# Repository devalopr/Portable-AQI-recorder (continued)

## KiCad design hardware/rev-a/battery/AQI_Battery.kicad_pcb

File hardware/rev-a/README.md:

# AQI recorder — Rev A engineering review

Implemented in KiCad 10. Main PCB: **44 × 80 mm**. Battery PCB: **44 × 90 mm**. Both use four copper layers, with In1.Cu reserved for ground. The checked KiCad files are the authoritative routed design.

| Project | Open in KiCad | Schematic PDF |
|---|---|---|
| Main board | [AQI_Main.kicad_pro](main/AQI_Main.kicad_pro) | [Main schematic](main/review/AQI_Main.pdf) |
| 18650 supply | [AQI_Battery.kicad_pro](battery/AQI_Battery.kicad_pro) | [Battery schematic](battery/review/AQI_Battery.pdf) |

For Fusion fit checks, import [AQI_Main-fit-check.step](main/review/AQI_Main-fit-check.step). This assembly includes the optional CO₂ and e-paper components. The external display, PM sensor body, cables and enclosure must be added separately. The switch model is a simplified envelope.

This is an engineering review version. Fabrication release still requires the electrical, assembly and enclosure items below. Gerbers and an assembly-order package are intentionally not included.

Main-board front/rear PNGs now show all optional components, including CO₂ and e-paper parts. DNP flags remain intact in the BOM. Enable “Models marked DNP” in KiCad’s 3D viewer Appearance panel (shortcut D); this is a live viewer setting, independent of the saved PCB. Sensirion’s official SCD4x model and a simplified, dimensioned C&K switch model are included locally. Board previews do not include the external display, PM module, enclosure or battery holder; the complete enclosure assembly still needs checking. Right/left placement is specified from the front/display view, so the rear image is mirrored.

## Main board

- ESP32-C3-MINI-1-H4, at the lower left, with its integrated antenna facing the bottom edge and copper keepout on every layer (x = 0–15.7 mm, y = 73.8–80 mm).
- TFT flex wraps around the top edge to the rear **TE 1-84953-0, 10-way, 1 mm, top-contact** connector. Contacts face away from the PCB, as verified by the user. J5 is 9 mm lower than the earlier placement (origin y = 16.85 mm). The approach from the top edge is clear of components; verify the actual flex bend radius and connector engagement in the enclosure. The display body envelope is on Dwgs.User.
- Three front switches at x = 8, 22 and 36 mm, y = 66.25 mm. The power switch is on the right edge below the CO₂ island (origin x = 41.7 mm, y = 65.2 mm), with its actuator projecting outward. It disables the switched 5 V rail and downstream regulators.
- Bottom-right USB-C and adjacent front-mounted battery GH connector (origins x = 38.3 mm and 24.3 mm respectively). USB-C provides standalone power and ESP32 native USB. A TS3USB30E data switch selects the local port when local VBUS is present; otherwise it selects the internal link. TPS2116 isolates the two power sources. The data paths disconnect when neither host is present.
- TPS62160 regulators provide nominal 3.2 V for the MCU/TFT and about 3.33 V for SEN6x. The reduced core voltage gives the TFT supply margin below its 3.3 V upper limit.
- STCS05A current sink provides PWM backlight dimming; 1.5 Ω sets about 67 mA nominal. Validate brightness, current and backlight compliance against the actual display.
- Separate SEN5x and SEN6x connectors on the right edge, both rotated to put their actual mating openings outward to the right, prevent interchange of their 5 V and 3.3 V cables. Attach **one PM module**; the shared sensor address is 0x69.
- Optional SCD41 sits on a rear-right island (sensor origin y = 53 mm; island and both SEN connectors moved upward 4 mm), with two enclosed isolation slots, a 3 × 2 mm electrical bridge and two permanent 1.5 mm-wide outer-edge support tabs. Ground/power pours stop at the bridge; only four 0.15 mm traces cross it (power, ground, SDA and SCL). The outer tabs contain no copper on any layer; they add mechanical support but increase heat conduction through the laminate. Its TPS7A20 regulator stays on the main PCB; C16 decouples the sensor locally and C42 bypasses the regulator output. This reduces heat conduction; it does not eliminate self-heating or enclosure airflow effects. The CO₂ circuit remains DNP in the default assembly.
- GDEY037T03 e-paper connector J6 is at the opposite (left) upper edge, with its flex entry facing outward; its external boost circuit is provided as an alternate population. The TFT and e-paper share SPI, CS, DC and RESET: fit one display.

## Battery board

- MPD BH-18650-PC holder for a standard 65 mm unprotected cell.
- DW01A plus Fortune FS8205A implement cell overcharge, overdischarge and overcurrent protection. The selected FS8205A uses the **4.4 × 3 mm TSSOP-8** footprint.
- BQ24074 charger with power path. Attach a **10 kΩ cell-contact NTC** at J4; do not substitute a fixed resistor for the required temperature monitoring in an enclosed battery product.
- Charger defaults to USB100. MCP23008 at 0x21 controls EN1/EN2 and reads charge/input-present status. Configured charge-current ceiling is approximately 0.8 A; actual charging is bounded by input limit, load and thermal regulation.
- TPS61023 produces nominal 5.045 V and has a physical output-enable switch. TPS63031 provides the auxiliary 3.3 V output. Generic header design targets are 5 V / 0.5 A and 3.3 V / 0.3 A; these and the main board share the input/cell power budget and require load/thermal qualification.
- MAX17048 at 0x36 reports cell voltage and estimated state of charge through the shared I2C bus. Firmware reads SOC register 0x04 as an unsigned 8.8 percentage value; clamp the displayed value to 0–100%. Validate the gauge model and temperature compensation with the chosen cell.
- Battery-side I2C pullups R18/R19 are DNP when connected to the main board. The main board supplies 3.2 V pullups.
- Cell-negative is isolated from system GND by the protection FETs. Do not bypass this separation with a cable, mounting hardware or an external ground connection.
- The holder requires correct polarity. Reverse-cell insertion protection is not implemented. The 3.3 V control supply remains active when the 5 V output switch is off; remove the cell for long-term storage.

## Internal cable

Use **JST GH 10-way**, side-entry SM10B-GHS-TB headers and matching GHR-10V-S housings/appropriate GH crimp contacts. Wire pin 1 to pin 1; verify continuity rather than relying on an off-the-shelf cable's apparent orientation. Start with a harness no longer than 50 mm, using suitable 26–28 AWG contacts/wire and a twisted D+/D− pair where practical. Check USB operation with the final harness.

| Pin | Signal | Direction |
|---|---|---|
| 1, 2 | Regulated 5 V | Battery → main |
| 3 | GND | Common |
| 4 | USB D− | Bidirectional |
| 5 | USB D+ | Bidirectional |
| 6 | GND | Common |
| 7 | I2C SDA | Bidirectional |
| 8 | I2C SCL | Main → battery |
| 9 | GND | Common |
| 10 | External USB host present | Battery → main |

The battery USB-C is a sink/data port. USB CC termination stays at each external receptacle; CC is not carried through GH. The main board's internal GH input is not another USB-C receptacle and needs no additional CC termination. Both external ports are isolated by the main-board switching circuits.

SEN5x J3: 1 = 5 V, 2 = GND, 3 = SDA, 4 = SCL, 5 = GND, 6 = NC. SEN6x J4 uses a **custom 4-to-6 cable**: 1 = 3.3 V, 2 = GND, 3 = SDA, 4 = SCL; sensor pins 5/6 remain open. Do not use the battery GH cable for a sensor.

## Display population

Default handheld assembly: populate J5 and the backlight circuit; leave e-paper parts DNP. The optional SCD41 circuit is separately selectable.

E-paper assembly: populate J6, L3, Q3, D10–D12, R30/R31 and C30–C36/C38–C41. Keep R32 fitted for the reference circuit's BS-low setting. J7 is a high-level override: remove R32 before bridging J7. Leave J5 and the backlight circuit unpopulated. Confirm the exact panel revision, flex thickness/contact orientation and BS setting against the purchased panel before assembly. The vendor pin table and reference drawing disagree about BS; this is a release item, not a resolved assumption.

The ESP32 pin allocation supports ESPHome. The exact GDEY037T03/UC8253 driver has not been validated in ESPHome; GxEPD2 has a panel driver, but using that Arduino driver does not by itself provide an ESPHome component. The repository's current prototype firmware also needs the Rev A GPIO map, MCP23008 buttons and fuel-gauge integration. See [firmware integration](firmware/README.md).

## Checks and release items

The final review includes KiCad ERC, DRC with schematic parity, an independent comparison of every connected pin against design.json, schematic PDFs, board renders and engineering BOMs. See [validation.json](validation.json) for actual results and checked file hashes. A clean DRC confirms geometry/connectivity rules; it does not validate a circuit's analogue performance or the enclosure.

Before fabrication release:

1. Finish the enclosure CAD: TFT bend radius, connector latch access, button caps/travel, PCB retention, sensor airflow and battery-holder clearance. No PCB mounting holes are included; the current outline assumes enclosure rails/retainers. Support the CO₂ island without a conductive metal bridge or force on the sensor. Check the isolation-slot tool radius and island strength with the fabricator; provide local enclosure support clear of the sensor opening.
2. Qualify the integrated antenna in the final enclosure. The TFT body spans x = 0.64–43.36 mm, y = 1.5–62.46 mm. The revised antenna spans approximately x = 2.4–15.6 mm, y = 74.1–79.5 mm, so it no longer lies behind the display. The nominal display-to-antenna gap is about 11.6 mm; the button and adjacent GH connector metal are closer. This 44 × 80 mm layout does **not** provide [Espressif's recommended 15 mm clearance in all directions](https://docs.espressif.com/projects/esp-hardware-design-guidelines/en/latest/esp32c3/pcb-layout-design.html#general-principles-of-pcb-layout-for-modules-positioning-a-module-on-a-base-board). Keep the cell, sensor bodies, cables, fasteners and enclosure metal away from the antenna. Measure Wi-Fi/BLE performance with the final LCD or e-paper assembly; copper keepouts alone do not establish RF performance. The integrated-antenna module is retained as requested; no external antenna substitution is made.
3. Qualify USB current and inrush. Standalone sensing requires a suitable 5 V supply (start with a rated 1 A or higher adapter). The main board does not detect Type-C advertised current. The battery board starts at 100 mA; firmware must establish the allowed source current before selecting 500 mA or resistor-programmed mode. Do not assume every host port permits 1 A. Verify boot/measurement with the battery absent and depleted, plus both-port plug/unplug transitions.
4. Review exact MLCC/inductor ordering codes, effective capacitance under DC bias, component substitutions and assembly availability. The CSVs are engineering BOMs, not approved JLCPCB assembly BOMs. In particular, verify the e-paper flying capacitor at its operating voltage.
5. Check battery protection thresholds against the selected cell, charge/discharge operation, cell NTC limits, output overload behaviour and temperatures in the enclosure. Review exposed-pad thermal vias and stencil/tenting with the assembler.
6. Validate CO₂ temperature offset with Wi-Fi, the display and PM sensor operating. Couple the CO₂ opening to ambient air and shield it from PM fan turbulence. Validate USB signal quality, regulator transients, backlight PWM, e-paper power sequencing/BS setting and the exact ESPHome display driver on hardware.

## Sources and reproducibility

The selected circuits were checked against manufacturer datasheets retained under references/datasheets. Main sources include [Espressif module documentation](https://documentation.espressif.com/esp32-c3-mini-1_datasheet_en.html), [TI BQ24074](https://www.ti.com/lit/ds/symlink/bq24074.pdf), [TI TPS61023](https://www.ti.com/lit/ds/symlink/tps61023.pdf), [ADI MAX17048](https://www.analog.com/media/en/technical-documentation/data-sheets/max17048-max17049.pdf), and the [Good Display reference document](https://ecksteinimg.de/Photo/GD03042/GDEY037T03-T02.pdf?_t=1768267937). [GxEPD2](https://github.com/ZinggJM/GxEPD2) lists the exact panel; the [ESPHome UC8253 discussion](https://github.com/orgs/esphome/discussions/3504) documents the integration gap.

Run `python3 scripts/refresh_review.py --render` with KiCad 10 installed to refresh checks, PDF/SVG/BOM exports and native board PNGs from the current KiCad files. The script accepts `--cli` and `--pcb-python` overrides; the latter must provide KiCad's pcbnew module. It does not regenerate the boards. Early research and construction helpers are retained for traceability; rebuilding from their intermediate inputs can erase or replace the manually finished routing.

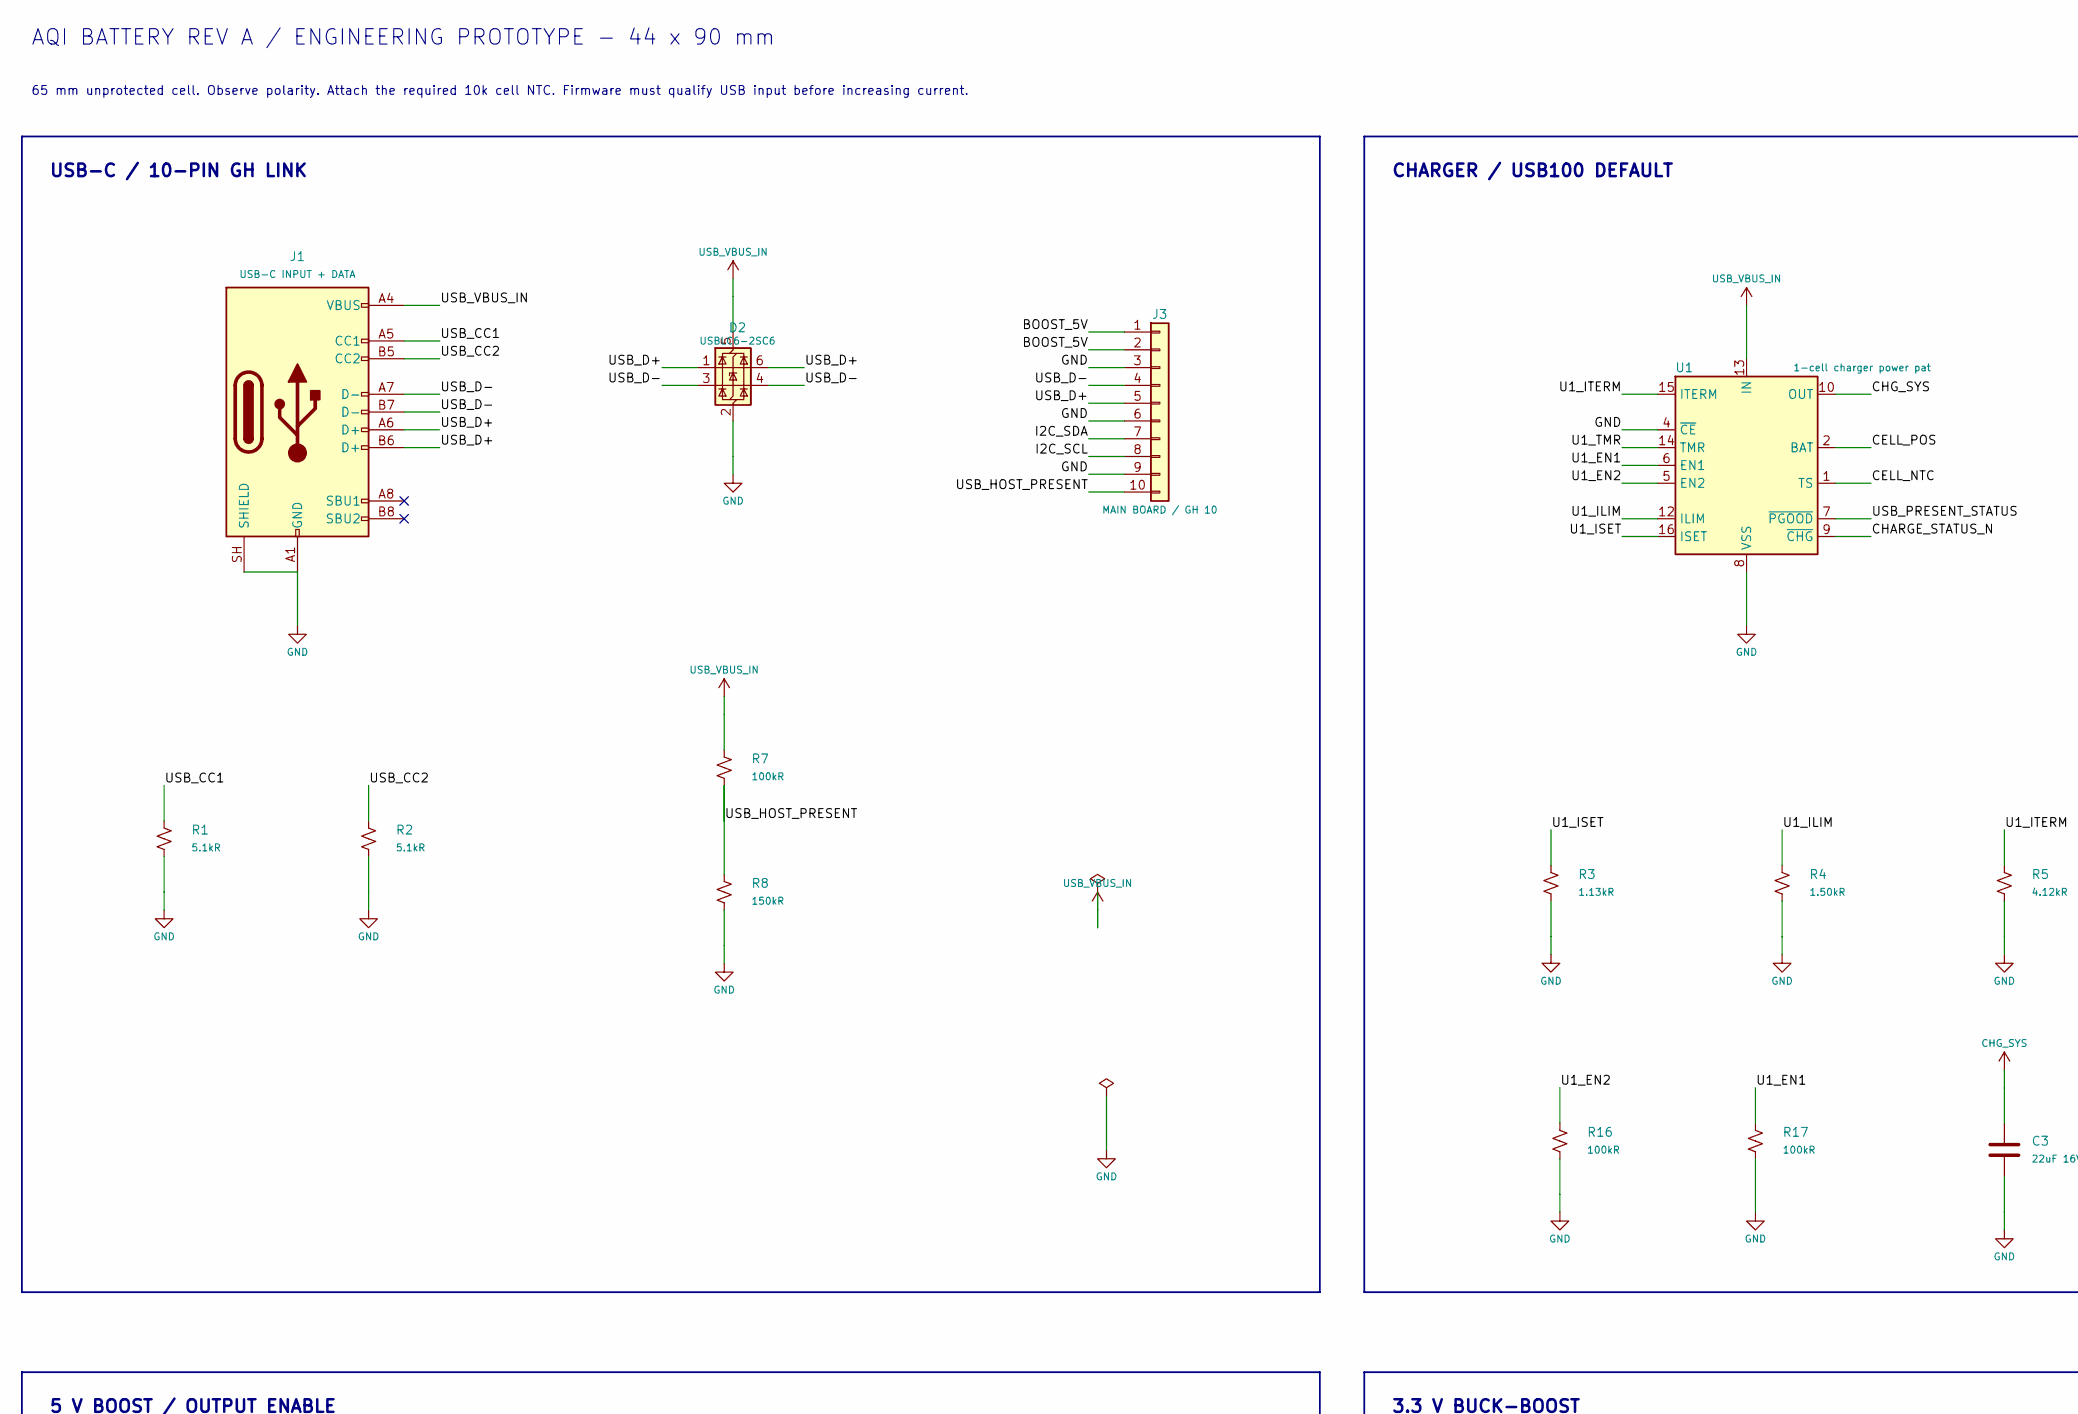
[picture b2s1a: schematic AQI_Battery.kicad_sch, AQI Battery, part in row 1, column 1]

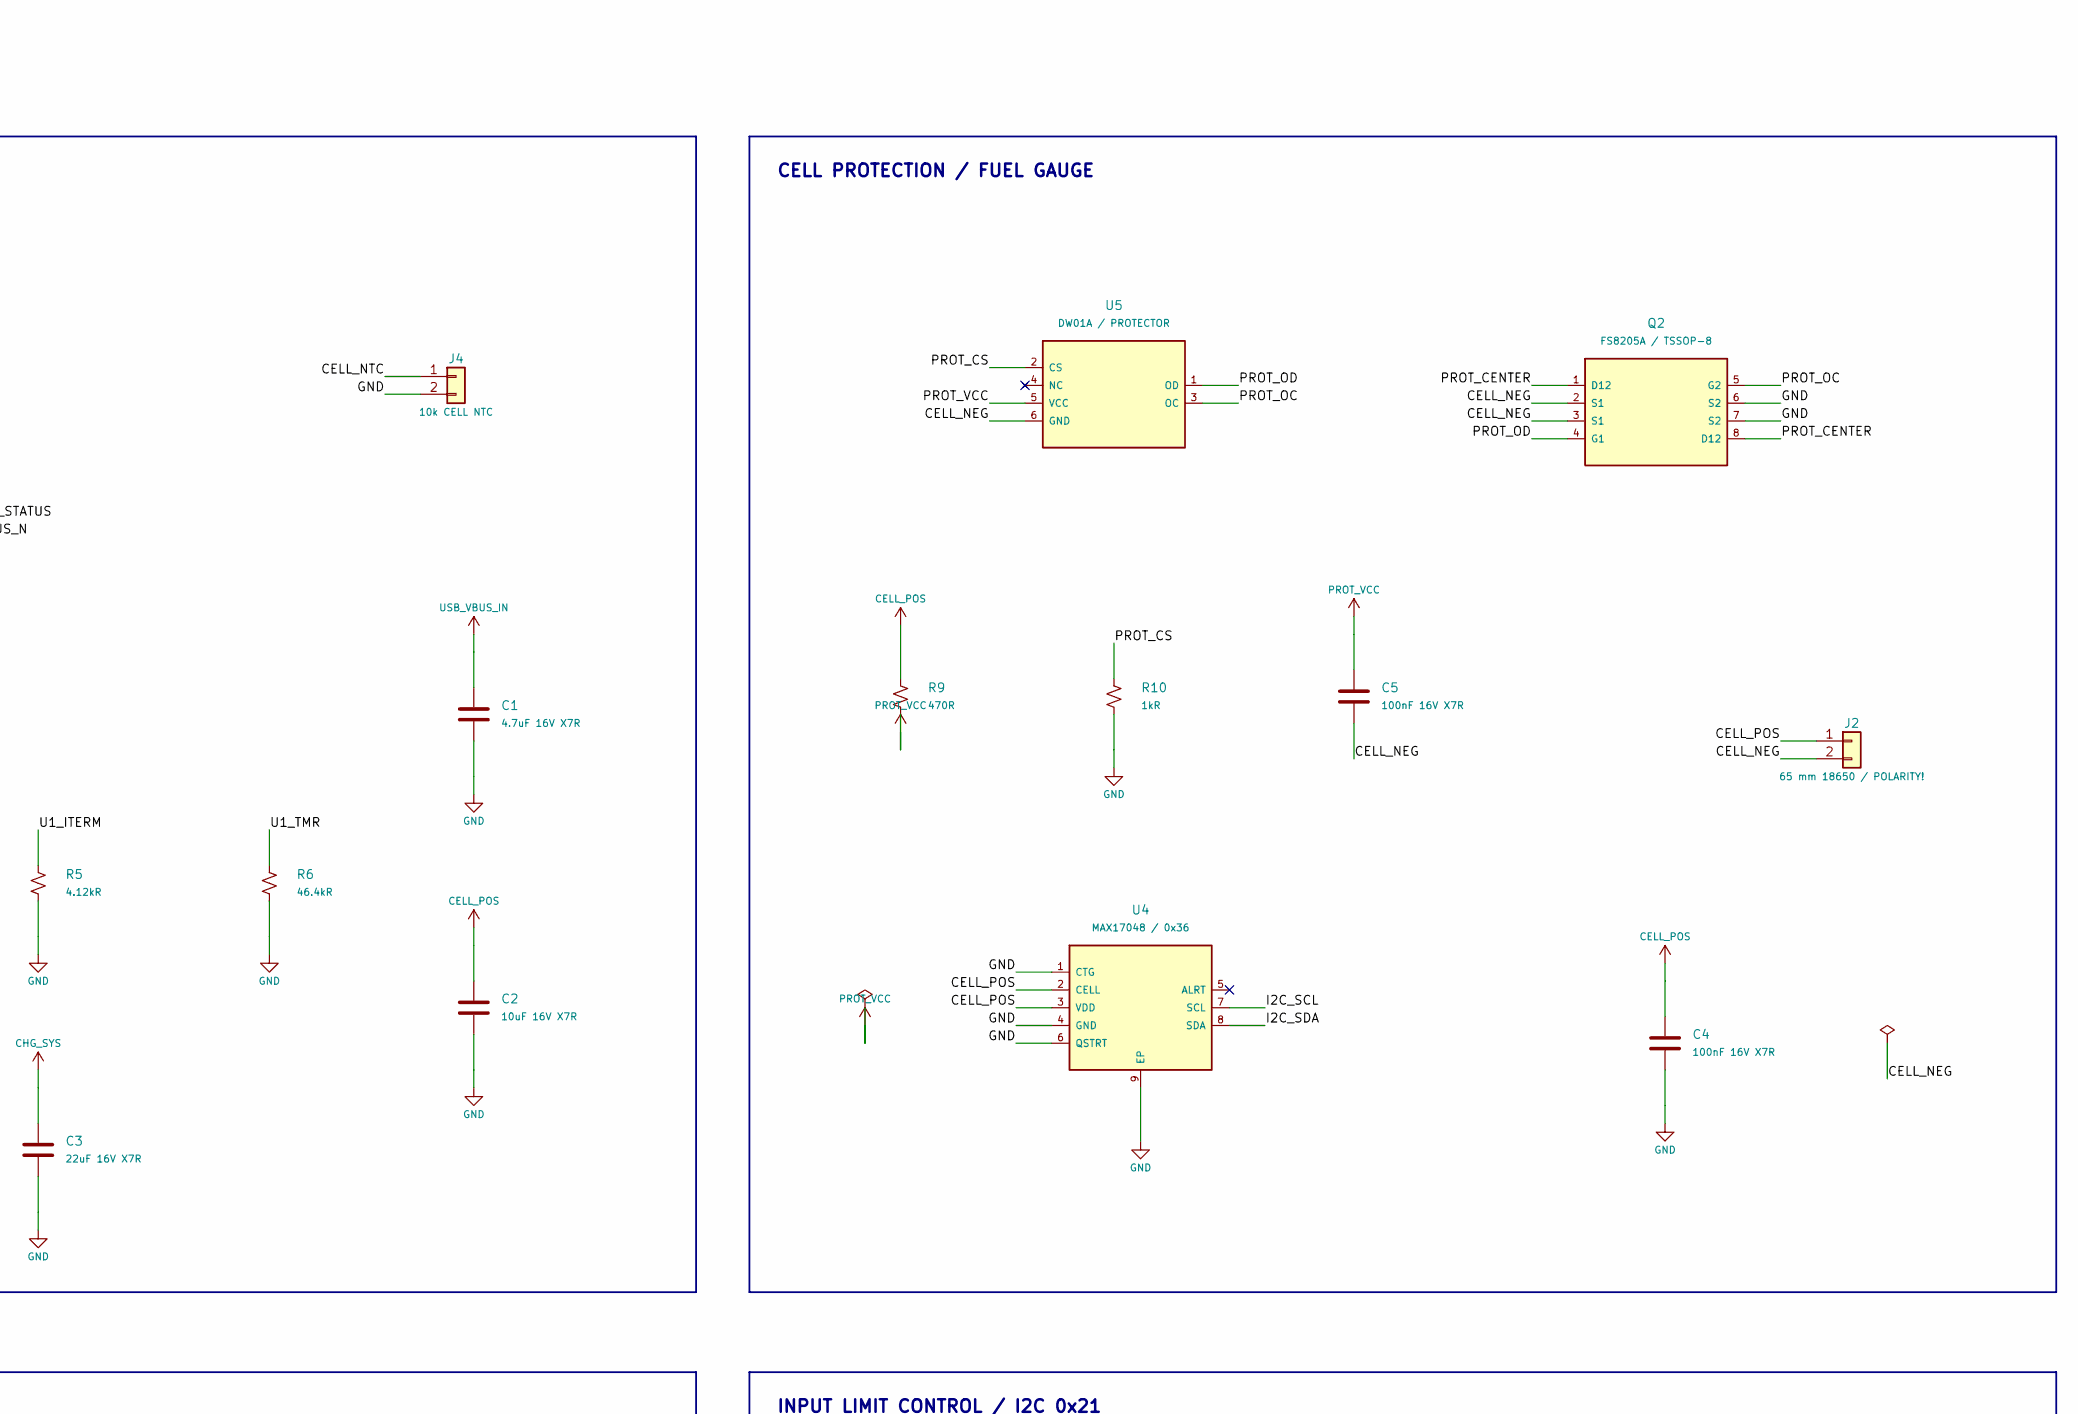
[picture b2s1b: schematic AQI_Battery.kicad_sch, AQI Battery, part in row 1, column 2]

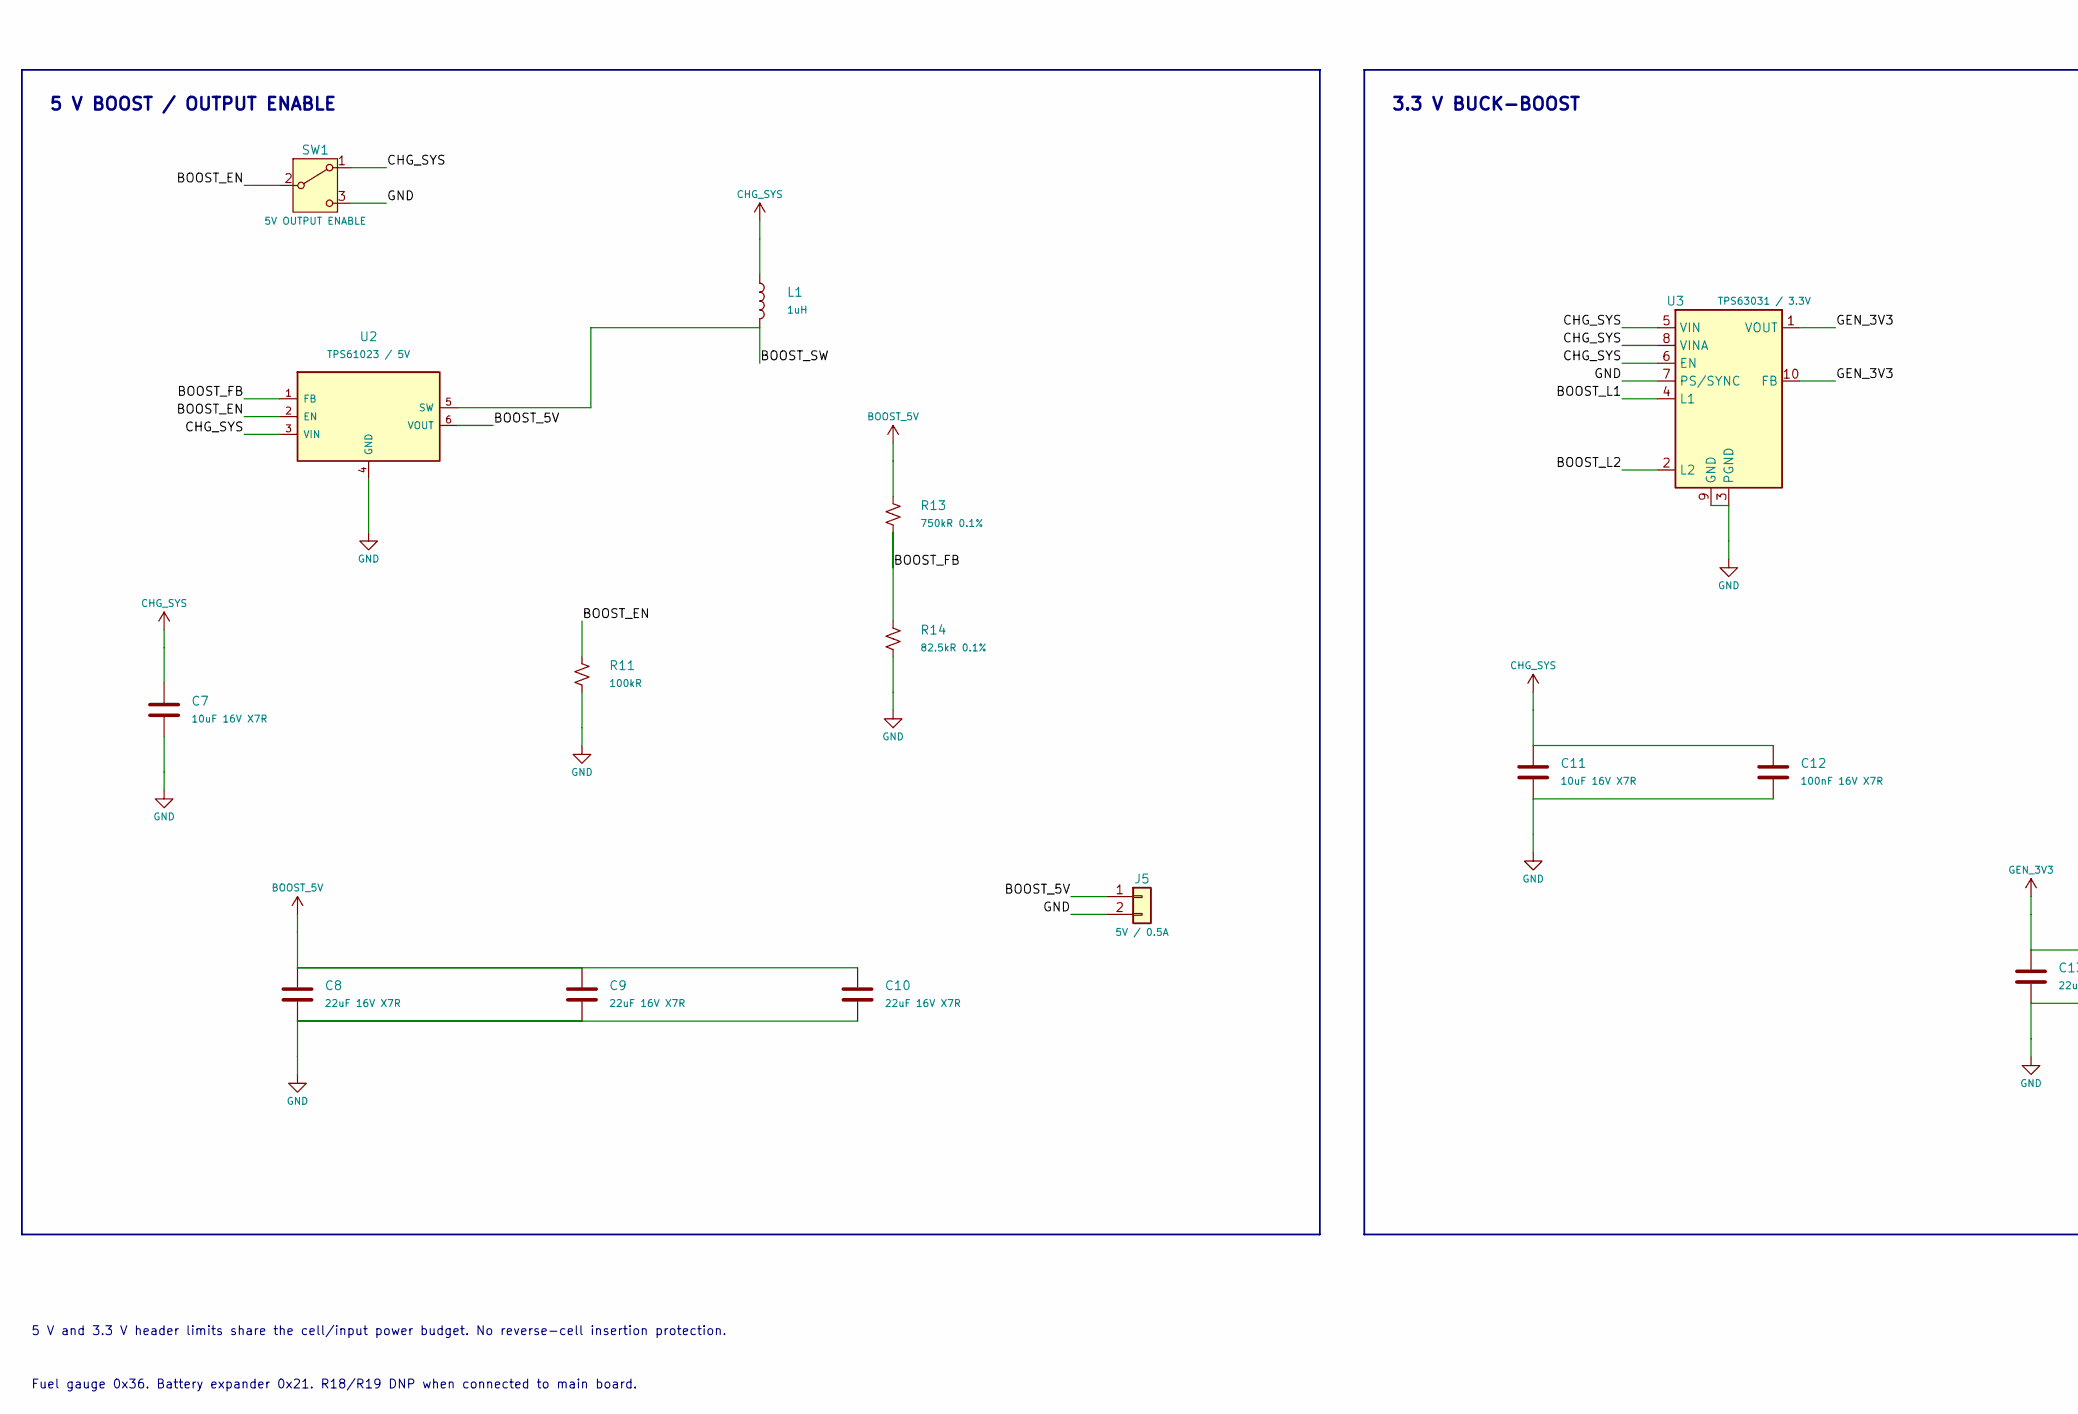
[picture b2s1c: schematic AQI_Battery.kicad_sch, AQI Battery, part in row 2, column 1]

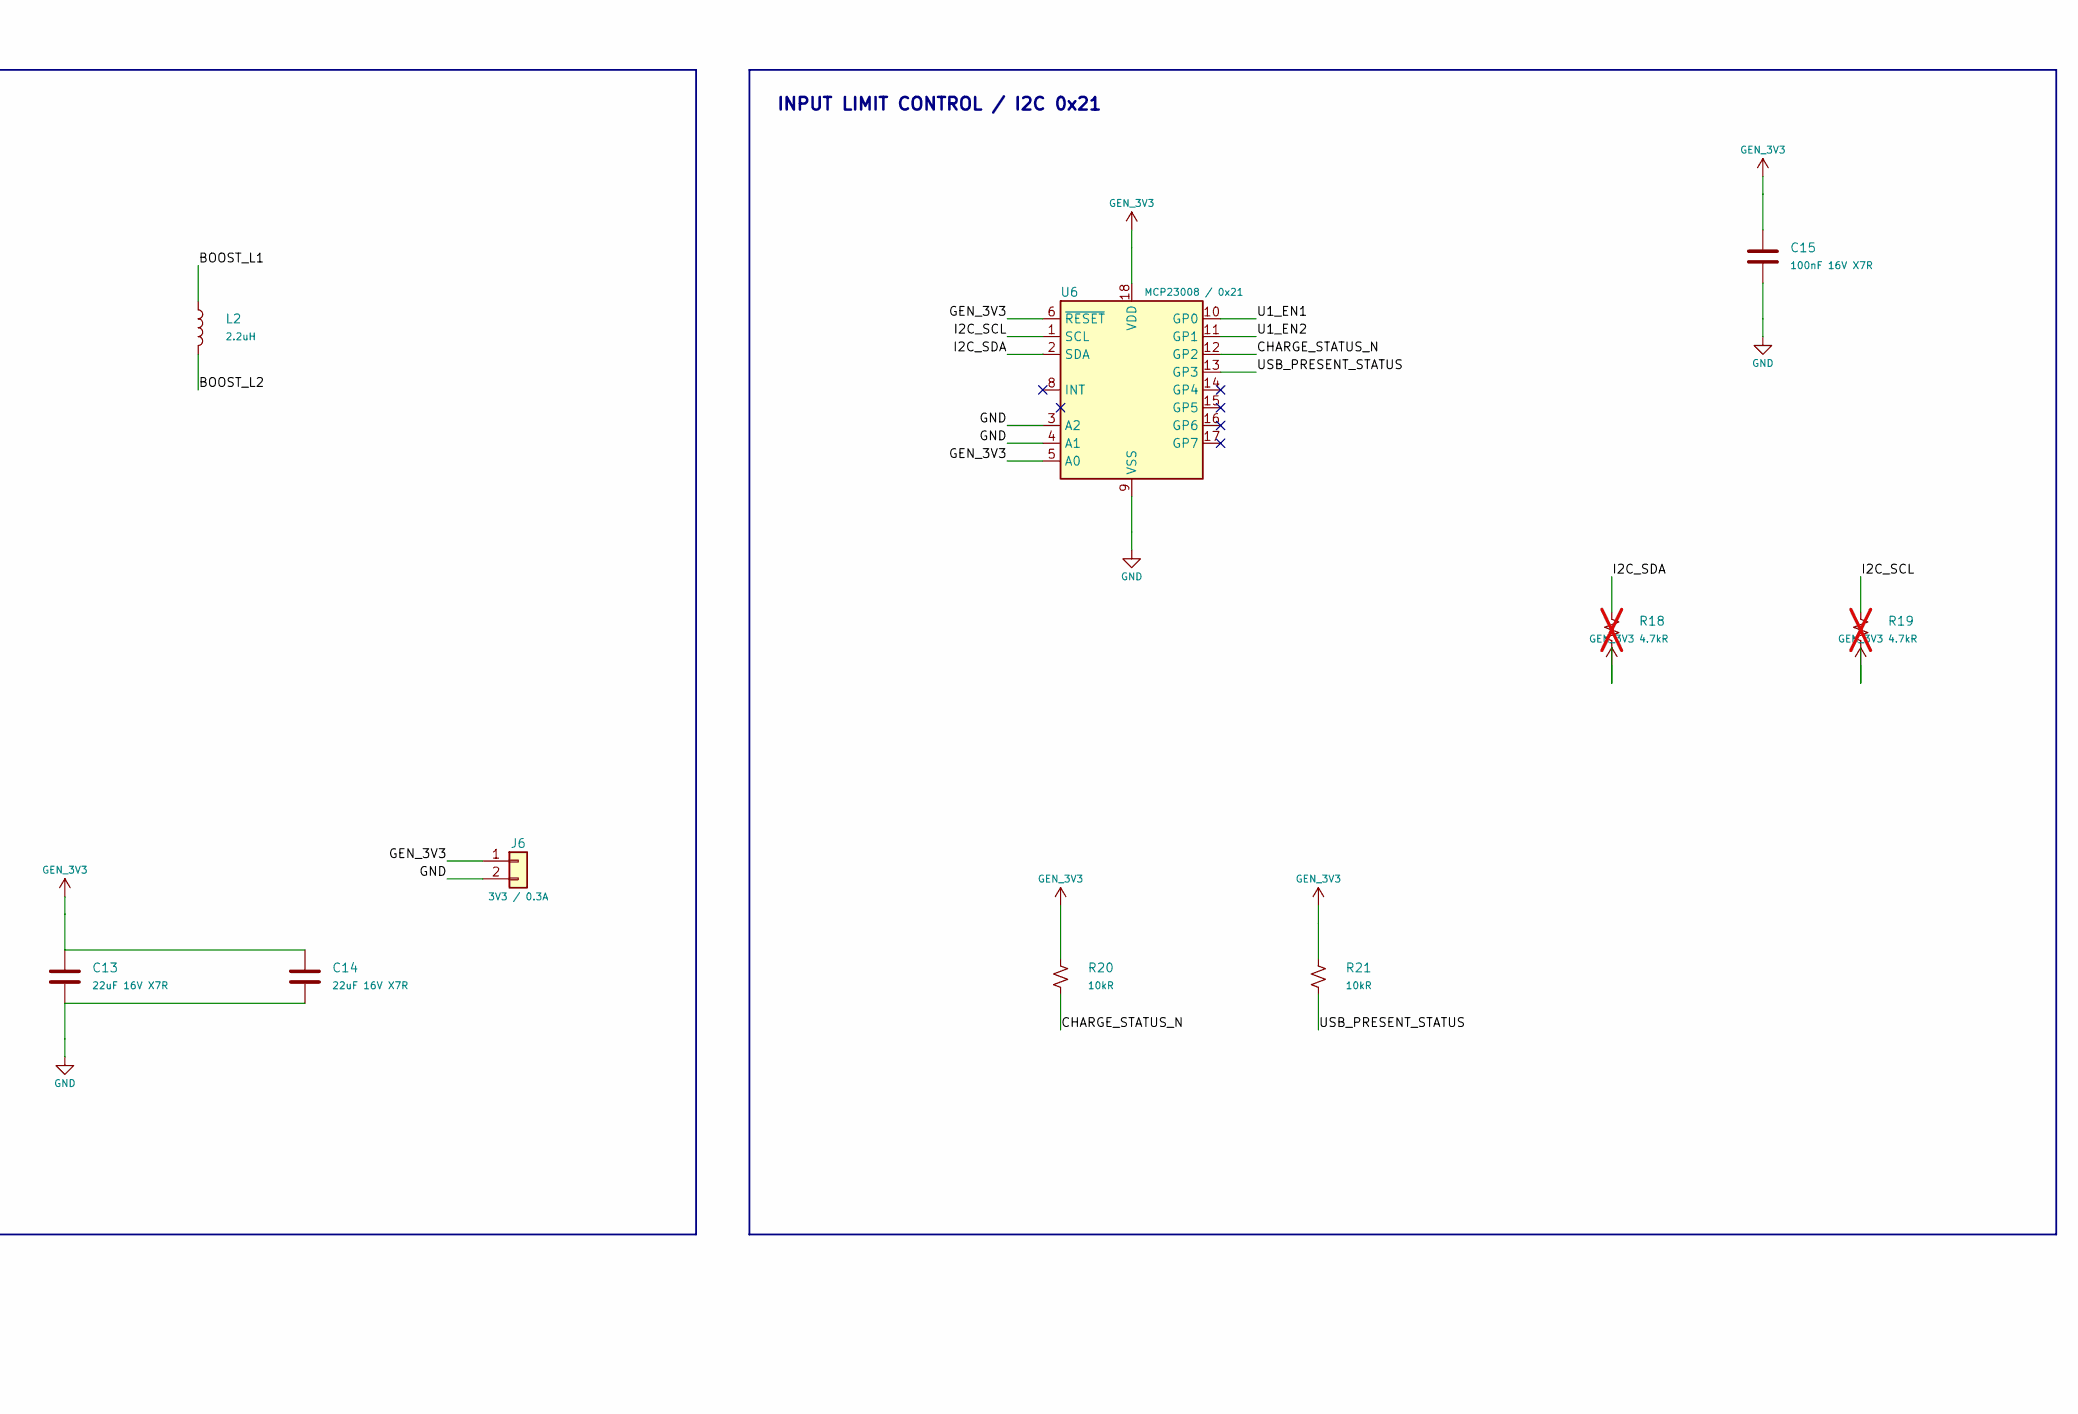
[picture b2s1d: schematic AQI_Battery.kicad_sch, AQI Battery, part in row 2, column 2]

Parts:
C1: 4.7uF 16V X7R; C_0805_2012Metric; MPN TBD
C2, C7, C11: 10uF 16V X7R; C_0805_2012Metric; MPN TBD
C3, C8, C9, C10, C13, C14: 22uF 16V X7R; C_0805_2012Metric; MPN TBD
C4, C5, C12: 100nF 16V X7R; C_0603_1608Metric; MPN TBD
C15: 100nF 16V X7R; C_0603_1608Metric
D2: USBLC6-2SC6; SOT-23-6; MPN USBLC6-2SC6
J1: USB-C INPUT + DATA; USB_C_Receptacle_GCT_USB4105-xx-A_16P_TopMnt_Horizontal; MPN USB4105-GF-A
J2: 65 mm 18650 / POLARITY!; BatteryHolder_MPD_BH-18650-PC; MPN BH-18650-PC
J3: MAIN BOARD / GH 10; JST_GH_SM10B-GHS-TB_1x10-1MP_P1.25mm_Horizontal; MPN SM10B-GHS-TB
J4: 10k CELL NTC; JST_GH_SM02B-GHS-TB_1x02-1MP_P1.25mm_Horizontal; MPN SM02B-GHS-TB(LF)(SN)
J5: 5V / 0.5A; PinHeader_1x02_P2.54mm_Vertical; MPN Pin header 1x2 P2.54
J6: 3V3 / 0.3A; PinHeader_1x02_P2.54mm_Vertical; MPN Pin header 1x2 P2.54
L1: 1uH; L_Coilcraft_XAL5030-XXX; MPN XAL5030-102MEC
L2: 2.2uH; L_Coilcraft_XAL4020-XXX; MPN XAL4020-222MEC
Q2: FS8205A / TSSOP-8; TSSOP-8_4.4x3mm_P0.65mm; MPN FS8205A
R1, R2: 5.1kR; R_0603_1608Metric; MPN TBD
R3: 1.13kR; R_0603_1608Metric; MPN TBD
R4: 1.50kR; R_0603_1608Metric; MPN TBD
R5: 4.12kR; R_0603_1608Metric; MPN TBD
R6: 46.4kR; R_0603_1608Metric; MPN TBD
R7, R11, R16, R17: 100kR; R_0603_1608Metric; MPN TBD
R8: 150kR; R_0603_1608Metric; MPN TBD
R9: 470R; R_0603_1608Metric; MPN TBD
R10: 1kR; R_0603_1608Metric; MPN TBD
R13: 750kR 0.1%; R_0603_1608Metric; MPN TBD
R14: 82.5kR 0.1%; R_0603_1608Metric; MPN TBD
R18, R19: 4.7kR; R_0603_1608Metric; MPN TBD; not fitted
R20, R21: 10kR; R_0603_1608Metric
SW1: 5V OUTPUT ENABLE; SW_SPDT_CK_JS102011SAQN; MPN JS102011SAQN
U1: 1-cell charger power pat; VQFN-16-1EP_3x3mm_P0.5mm_EP1.6x1.6mm; MPN BQ24074RGT
U2: TPS61023 / 5V; SOT-563; MPN TPS61023DRLR
U3: TPS63031 / 3.3V; WSON-10-1EP_2.5x2.5mm_P0.5mm_EP1.2x2mm; MPN TPS63031DSKR
U4: MAX17048 / 0x36; TDFN-8-1EP_2x2mm_P0.5mm_EP0.8x1.2mm; MPN MAX17048G+T10
U5: DW01A / PROTECTOR; SOT-23-6; MPN DW01A
U6: MCP23008 / 0x21; SOIC-18W_7.5x11.6mm_P1.27mm; MPN MCP23008T-E/SO

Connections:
/BOOST_EN: R11.1, SW1.2 (B), U2.2 (EN)
/BOOST_FB: R13.2, R14.1, U2.1 (FB)
/BOOST_L1: L2.1, U3.4 (L1)
/BOOST_L2: L2.2, U3.2 (L2)
/BOOST_SW: L1.2, U2.5 (SW)
/CELL_NEG: C5.2, J2.2, Q2.2 (S1), Q2.3 (S1), U5.6 (GND)
/CELL_NTC: J4.1, U1.1 (TS)
/CHARGE_STATUS_N: R20.2, U1.9 (~CHG), U6.12 (GP2)
/I2C_SCL: J3.8, R19.1, U4.7 (SCL), U6.1 (SCL)
/I2C_SDA: J3.7, R18.1, U4.8 (SDA), U6.2 (SDA)
/PROT_CENTER: Q2.1 (D12), Q2.8 (D12)
/PROT_CS: R10.1, U5.2 (CS)
/PROT_OC: Q2.5 (G2), U5.3 (OC)
/PROT_OD: Q2.4 (G1), U5.1 (OD)
/U1_EN1: R17.1, U1.6 (EN1), U6.10 (GP0)
/U1_EN2: R16.1, U1.5 (EN2), U6.11 (GP1)
/U1_ILIM: R4.1, U1.12 (ILIM)
/U1_ISET: R3.1, U1.16 (ISET)
/U1_ITERM: R5.1, U1.15 (ITERM)
/U1_TMR: R6.1, U1.14 (TMR)
/USB_CC1: J1.A5 (CC1), R1.1
/USB_CC2: J1.B5 (CC2), R2.1
/USB_D+: D2.1 (I/O1), D2.6 (I/O1), J1.A6 (D+), J1.B6 (D+), J3.5
/USB_D-: D2.3 (I/O2), D2.4 (I/O2), J1.A7 (D-), J1.B7 (D-), J3.4
/USB_HOST_PRESENT: J3.10, R7.2, R8.1
/USB_PRESENT_STATUS: R21.2, U1.7 (~PGOOD), U6.13 (GP3)
BOOST_5V: C8.1, C9.1, C10.1, J3.1, J3.2, J5.1, R13.1, U2.6 (VOUT)
CELL_POS: C2.1, C4.1, J2.1, R9.1, U1.2 (BAT), U1.3 (BAT), U4.2 (CELL), U4.3 (VDD)
CHG_SYS: C3.1, C7.1, C11.1, C12.1, L1.1, SW1.1 (A), U1.10 (OUT), U1.11 (OUT), U2.3 (VIN), U3.5 (VIN), U3.6 (EN), U3.8 (VINA)
GEN_3V3: C13.1, C14.1, C15.1, J6.1, R18.2, R19.2, R20.1, R21.1, U3.1 (VOUT), U3.10 (FB), U6.5 (A0), U6.6 (~RESET), U6.18 (VDD)
GND: C1.2, C2.2, C3.2, C4.2, C7.2, C8.2, C9.2, C10.2, C11.2, C12.2, C13.2, C14.2, C15.2, D2.2 (GND), J1.A1 (GND), J1.A12 (GND), J1.B1 (GND), J1.B12 (GND), J1.SH (SHIELD), J3.3, J3.6, J3.9, J4.2, J5.2, J6.2, Q2.6 (S2), Q2.7 (S2), R1.2, R2.2, R3.2, R4.2, R5.2, R6.2, R8.2, R10.2, R11.2, R14.2, R16.2, R17.2, SW1.3 (C), U1.4 (~CE), U1.8 (VSS), U1.17 (VSS), U2.4 (GND), U3.3 (PGND), U3.7 (PS/SYNC), U3.9 (GND), U3.11 (PGND), U4.1 (CTG), U4.4 (GND), U4.6 (QSTRT), U4.9 (EP), U6.3 (A2), U6.4 (A1), U6.9 (VSS)
PROT_VCC: C5.1, R9.2, U5.5 (VCC)
USB_VBUS_IN: C1.1, D2.5 (VBUS), J1.A4 (VBUS), J1.A9 (VBUS), J1.B4 (VBUS), J1.B9 (VBUS), R7.1, U1.13 (IN)

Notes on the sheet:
USB-C / 10-PIN GH LINK
CHARGER / USB100 DEFAULT
CELL PROTECTION / FUEL GAUGE
5 V BOOST / OUTPUT ENABLE
3.3 V BUCK-BOOST
INPUT LIMIT CONTROL / I2C 0x21
AQI BATTERY REV A / ENGINEERING PROTOTYPE - 44 x 90 mm
65 mm unprotected cell. Observe polarity. Attach the required 10k cell NTC. Firmware must qualify USB input before increasing current.
5 V and 3.3 V header limits share the cell/input power budget. No reverse-cell insertion protection.
Fuel gauge 0x36. Battery expander 0x21. R18/R19 DNP when connected to main board.

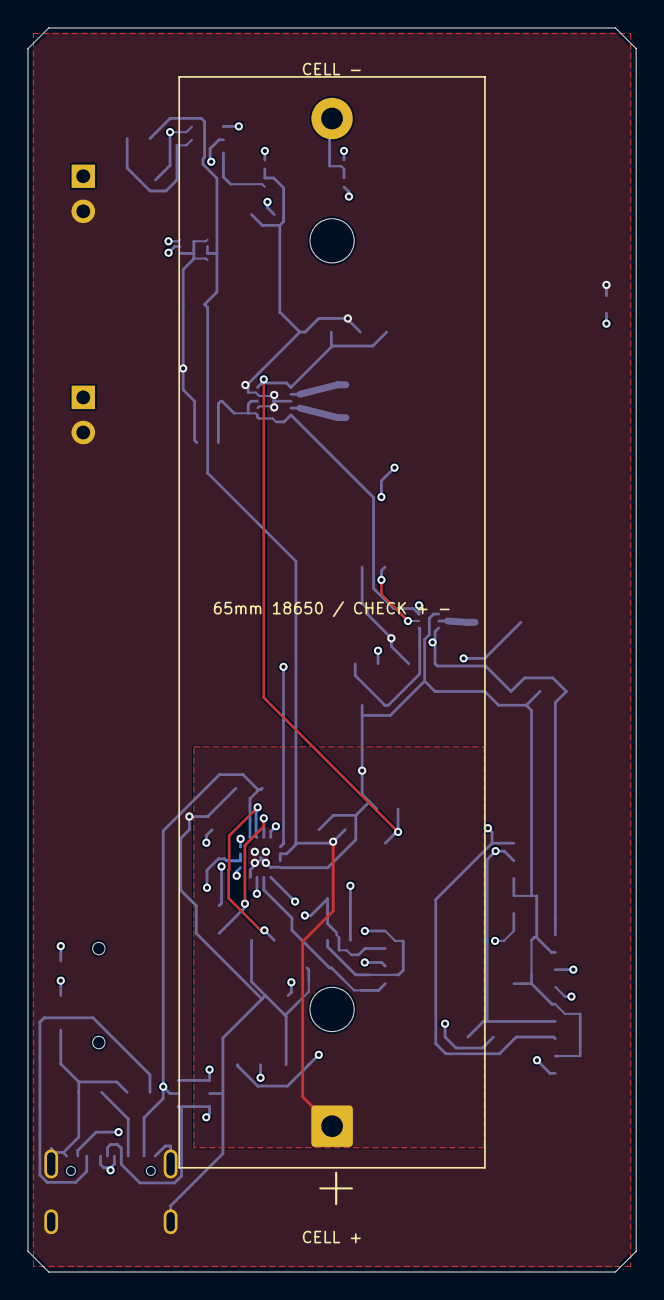
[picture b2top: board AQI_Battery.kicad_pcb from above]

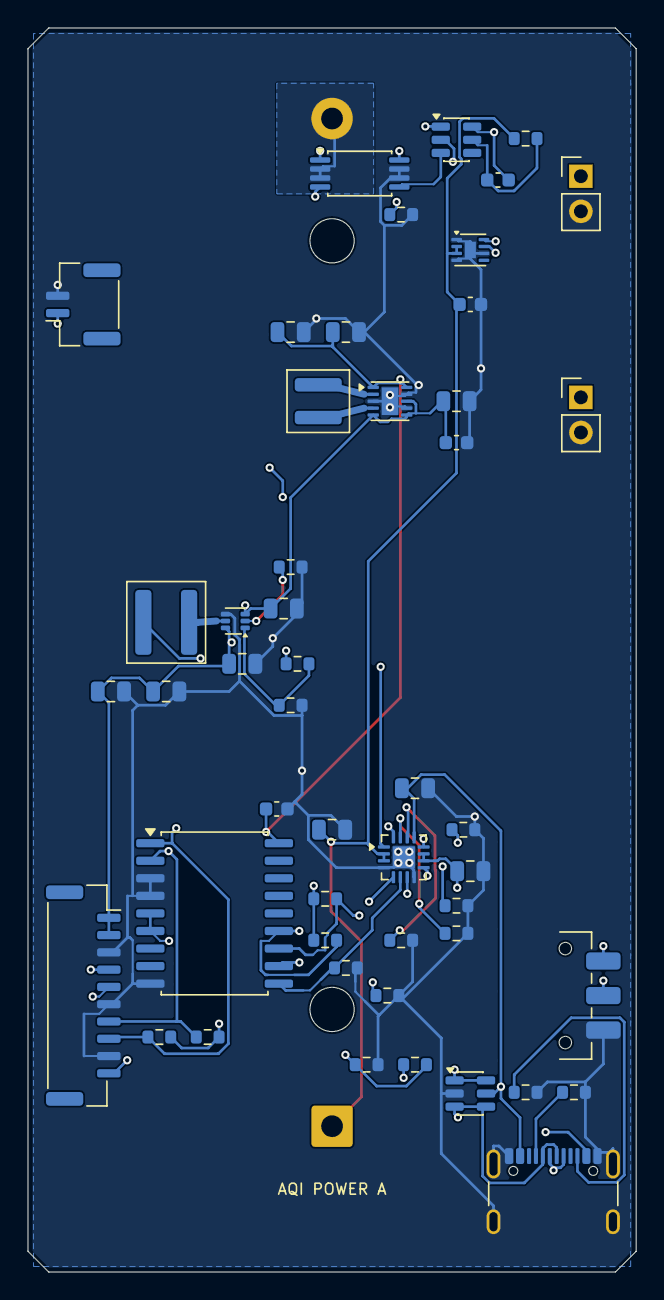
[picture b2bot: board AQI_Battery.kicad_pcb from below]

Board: 4 copper layers, 44.0 x 90.0 mm, 50 parts (49 on the bottom side), 33 nets.

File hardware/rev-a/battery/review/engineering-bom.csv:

"Reference","Value","MPN","Manufacturer","Footprint","DNP","Datasheet","Assembly note"
"C1","4.7uF 16V X7R","TBD","TBD","Capacitor_SMD:C_0805_2012Metric","","",""
"C2","10uF 16V X7R","TBD","TBD","Capacitor_SMD:C_0805_2012Metric","","",""
"C3","22uF 16V X7R","TBD","TBD","Capacitor_SMD:C_0805_2012Metric","","",""
"C4","100nF 16V X7R","TBD","TBD","Capacitor_SMD:C_0603_1608Metric","","",""
"C5","100nF 16V X7R","TBD","TBD","Capacitor_SMD:C_0603_1608Metric","","",""
"C7","10uF 16V X7R","TBD","TBD","Capacitor_SMD:C_0805_2012Metric","","",""
"C8","22uF 16V X7R","TBD","TBD","Capacitor_SMD:C_0805_2012Metric","","",""
"C9","22uF 16V X7R","TBD","TBD","Capacitor_SMD:C_0805_2012Metric","","",""
"C10","22uF 16V X7R","TBD","TBD","Capacitor_SMD:C_0805_2012Metric","","",""
"C11","10uF 16V X7R","TBD","TBD","Capacitor_SMD:C_0805_2012Metric","","",""
"C12","100nF 16V X7R","TBD","TBD","Capacitor_SMD:C_0603_1608Metric","","",""
"C13","22uF 16V X7R","TBD","TBD","Capacitor_SMD:C_0805_2012Metric","","",""
"C14","22uF 16V X7R","TBD","TBD","Capacitor_SMD:C_0805_2012Metric","","",""
"C15","100nF 16V X7R","","","Capacitor_SMD:C_0603_1608Metric","","",""
"D2","USBLC6-2SC6","USBLC6-2SC6","STMicroelectronics","Package_TO_SOT_SMD:SOT-23-6","","",""
"J1","USB-C INPUT + DATA","USB4105-GF-A","GCT","Connector_USB:USB_C_Receptacle_GCT_USB4105-xx-A_16P_TopMnt_Horizontal","","https://gctronic.com/PDF/USB4105-GF-A.pdf",""
"J2","65 mm 18650 / POLARITY!","BH-18650-PC","MPD","Battery:BatteryHolder_MPD_BH-18650-PC","","",""
"J3","MAIN BOARD / GH 10","SM10B-GHS-TB","JST","Connector_JST:JST_GH_SM10B-GHS-TB_1x10-1MP_P1.25mm_Horizontal","","https://www.jst-mfg.com/product/pdf/eng/eGH.pdf",""
"J4","10k CELL NTC","SM02B-GHS-TB(LF)(SN)","JST","Connector_JST:JST_GH_SM02B-GHS-TB_1x02-1MP_P1.25mm_Horizontal","","",""
"J5","5V / 0.5A","Pin header 1x2 P2.54","Generic","Connector_PinHeader_2.54mm:PinHeader_1x02_P2.54mm_Vertical","","",""
"J6","3V3 / 0.3A","Pin header 1x2 P2.54","Generic","Connector_PinHeader_2.54mm:PinHeader_1x02_P2.54mm_Vertical","","",""
"L1","1uH","XAL5030-102MEC","Coilcraft","Inductor_SMD:L_Coilcraft_XAL5030-XXX","","https://www.coilcraft.com/en-us/products/power/shielded-indu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",""
"L2","2.2uH","XAL4020-222MEC","Coilcraft","Inductor_SMD:L_Coilcraft_XAL4020-XXX","","https://www.coilcraft.com/en-us/products/power/high-voltage-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",""
"Q2","FS8205A / TSSOP-8","FS8205A","Fortune Semiconductor","Package_SO:TSSOP-8_4.4x3mm_P0.65mm","","https://jgamblog.wordpress.com/wp-content/uploads/2017/01/fs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",""
"R1","5.1kR","TBD","TBD","Resistor_SMD:R_0603_1608Metric","","",""
"R2","5.1kR","TBD","TBD","Resistor_SMD:R_0603_1608Metric","","",""
"R3","1.13kR","TBD","TBD","Resistor_SMD:R_0603_1608Metric","","",""
"R4","1.50kR","TBD","TBD","Resistor_SMD:R_0603_1608Metric","","",""
"R5","4.12kR","TBD","TBD","Resistor_SMD:R_0603_1608Metric","","",""
"R6","46.4kR","TBD","TBD","Resistor_SMD:R_0603_1608Metric","","",""
"R7","100kR","TBD","TBD","Resistor_SMD:R_0603_1608Metric","","",""
"R8","150kR","TBD","TBD","Resistor_SMD:R_0603_1608Metric","","",""
"R9","470R","TBD","TBD","Resistor_SMD:R_0603_1608Metric","","",""
"R10","1kR","TBD","TBD","Resistor_SMD:R_0603_1608Metric","","",""
"R11","100kR","TBD","TBD","Resistor_SMD:R_0603_1608Metric","","",""
"R13","750kR 0.1%","TBD","TBD","Resistor_SMD:R_0603_1608Metric","","",""
"R14","82.5kR 0.1%","TBD","TBD","Resistor_SMD:R_0603_1608Metric","","",""
"R16","100kR","TBD","TBD","Resistor_SMD:R_0603_1608Metric","","",""
"R17","100kR","TBD","TBD","Resistor_SMD:R_0603_1608Metric","","",""
"R18","4.7kR","TBD","TBD","Resistor_SMD:R_0603_1608Metric","DNP","","Populate only for independent I2C operation. Main PCB supplies the pullups."
"R19","4.7kR","TBD","TBD","Resistor_SMD:R_0603_1608Metric","DNP","","Populate only for independent I2C operation. Main PCB supplies the pullups."
"R20","10kR","","","Resistor_SMD:R_0603_1608Metric","","",""
"R21","10kR","","","Resistor_SMD:R_0603_1608Metric","","",""
"SW1","5V OUTPUT ENABLE","JS102011SAQN","C&K","Button_Switch_SMD:SW_SPDT_CK_JS102011SAQN","","",""
"U1","1-cell charger power pat","BQ24074RGT","Texas Instruments","Package_DFN_QFN:VQFN-16-1EP_3x3mm_P0.5mm_EP1.6x1.6mm","","https://www.ti.com/lit/ds/symlink/bq24074.pdf",""
"U2","TPS61023 / 5V","TPS61023DRLR","Texas Instruments","Package_TO_SOT_SMD:SOT-563","","https://www.ti.com/lit/ds/symlink/tps61023.pdf",""
"U3","TPS63031 / 3.3V","TPS63031DSKR","Texas Instruments","Package_SON:WSON-10-1EP_2.5x2.5mm_P0.5mm_EP1.2x2mm","","https://www.ti.com/lit/ds/symlink/tps63031.pdf",""
"U4","MAX17048 / 0x36","MAX17048G+T10","Analog Devices","Package_DFN_QFN:TDFN-8-1EP_2x2mm_P0.5mm_EP0.8x1.2mm","","https://www.analog.com/media/en/technical-documentation/data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",""
"U5","DW01A / PROTECTOR","DW01A","Tani","Package_TO_SOT_SMD:SOT-23-6","","https://www.tanisemi.com/Data/tanisemi/upload/file/20241211/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","Exact Tani thresholds; never substitute without checking voltage thresholds and delay times."
"U6","MCP23008 / 0x21","MCP23008T-E/SO","Microchip","Package_SO:SOIC-18W_7.5x11.6mm_P1.27mm","","https://ww1.microchip.com/downloads/aemDocuments/documents/O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",""
